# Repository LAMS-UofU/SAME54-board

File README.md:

# LAMS 

In these files, you will find the software, datasheets and PCB design for the LAMS project. We integrated multiple peripherals to use with our needed devices such as: timers for the servo PWM signal, UART communications for the LiDAR, simple GPIO signals for a status LED, as well as a simple SysTick configuration to give precise timing measurements. 

## Pinouts

LiDAR: Tx (PA04) / Rx (PA05) / PWM (PB09) <br>
Servo: PWM (PA07) <br>
SD Card: CMD (PA20) / CLK (PA21) / DAT0 (PB18) / DAT1 (PB19) / DAT2 (PB20) / DAT3 (PB21) / CD (PD20) / WP (PD21) <br>
Status LED: PA06 <br>
Start Button: PA27 <br>

## Resources

### SAME54

[SAM D5X/E5X Family Datasheet](http://ww1.microchip.com/downloads/en/DeviceDoc/SAM_D5xE5x_Family_Data_Sheet_DS60001507F.pdf) <br>
[SAM E54 Xplained Pro User's Guide](http://ww1.microchip.com/downloads/en/DeviceDoc/70005321A.pdf)

### Peripherals

[RPLiDAR A2M8 Datasheet](https://cdn.sparkfun.com/assets/e/a/f/9/8/LD208_SLAMTEC_rplidar_datasheet_A2M8_v1.0_en.pdf) <br>
[RPLiDAR A2M8 Communications Protocol v1.0](https://www.robotshop.com/media/files/pdf2/rpk-02-communication-protocol.pdf) <br>
[RPLiDAR A2M8 Communications Protocol v2.1](http://bucket.download.slamtec.com/ccb3c2fc1e66bb00bd4370e208b670217c8b55fa/LR001_SLAMTEC_rplidar_protocol_v2.1_en.pdf) <br>
[SPT5435-180 Specifications](http://www.spt-servo.com/Product/015234339.html)

### MISC

[ASF4 API Reference Manual](http://ww1.microchip.com/downloads/en/DeviceDoc/50002633B.pdf)

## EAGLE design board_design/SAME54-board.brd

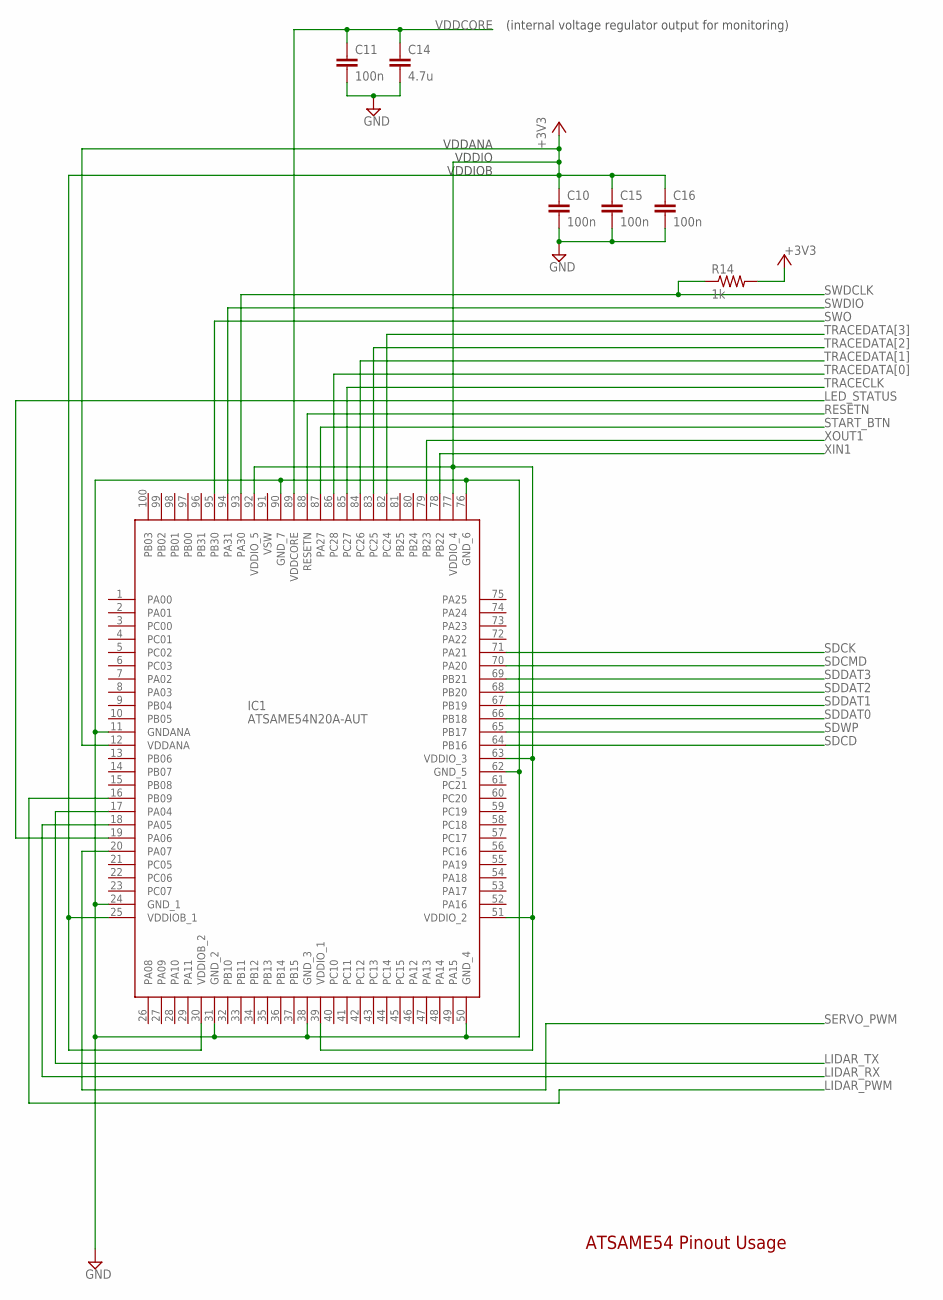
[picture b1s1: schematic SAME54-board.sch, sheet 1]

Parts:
C10, C11, C15, C16: 100n; C0603
C14: 4.7u; C0603
IC1: ATSAME54N20A-AUT; QFP50P1600X1600X120-100N
R14: 1k; R0603

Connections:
+3V3: C10.1, C15.1, C16.1, IC1.12 (VDDANA), IC1.25 (VDDIOB_1), IC1.30 (VDDIOB_2), IC1.39 (VDDIO_1), IC1.51 (VDDIO_2), IC1.63 (VDDIO_3), IC1.77 (VDDIO_4), IC1.92 (VDDIO_5), R14.2; also elsewhere on the board
GND: C10.2, C11.2, C14.2, C15.2, C16.2, IC1.11 (GNDANA), IC1.24 (GND_1), IC1.31 (GND_2), IC1.38 (GND_3), IC1.50 (GND_4), IC1.62 (GND_5), IC1.76 (GND_6), IC1.90 (GND_7); also elsewhere on the board
LED_STATUS: IC1.19 (PA06); also elsewhere on the board
LIDAR_PWM: IC1.16 (PB09); also elsewhere on the board
LIDAR_RX: IC1.18 (PA05); also elsewhere on the board
LIDAR_TX: IC1.17 (PA04); also elsewhere on the board
RESETN: IC1.88 (RESETN); also elsewhere on the board
SDCD: IC1.64 (PB16); also elsewhere on the board
SDCK: IC1.71 (PA21); also elsewhere on the board
SDCMD: IC1.70 (PA20); also elsewhere on the board
SDDAT0: IC1.66 (PB18); also elsewhere on the board
SDDAT1: IC1.67 (PB19); also elsewhere on the board
SDDAT2: IC1.68 (PB20); also elsewhere on the board
SDDAT3: IC1.69 (PB21); also elsewhere on the board
SDWP: IC1.65 (PB17); also elsewhere on the board
SERVO_PWM: IC1.20 (PA07); also elsewhere on the board
START_BTN: IC1.87 (PA27); also elsewhere on the board
SWDCLK: IC1.93 (PA30), R14.1; also elsewhere on the board
SWDIO: IC1.94 (PA31); also elsewhere on the board
SWO: IC1.95 (PB30); also elsewhere on the board
TRACECLK: IC1.85 (PC27); also elsewhere on the board
TRACEDATA[0]: IC1.86 (PC28); also elsewhere on the board
TRACEDATA[1]: IC1.84 (PC26); also elsewhere on the board
TRACEDATA[2]: IC1.83 (PC25); also elsewhere on the board
TRACEDATA[3]: IC1.82 (PC24); also elsewhere on the board
VDDCORE: C11.1, C14.1, IC1.89 (VDDCORE)
XIN1: IC1.78 (PB22); also elsewhere on the board
XOUT1: IC1.79 (PB23); also elsewhere on the board

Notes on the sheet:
ATSAME54 Pinout Usage
(internal voltage regulator output for monitoring)
VDDANA
VDDIO
VDDIOB

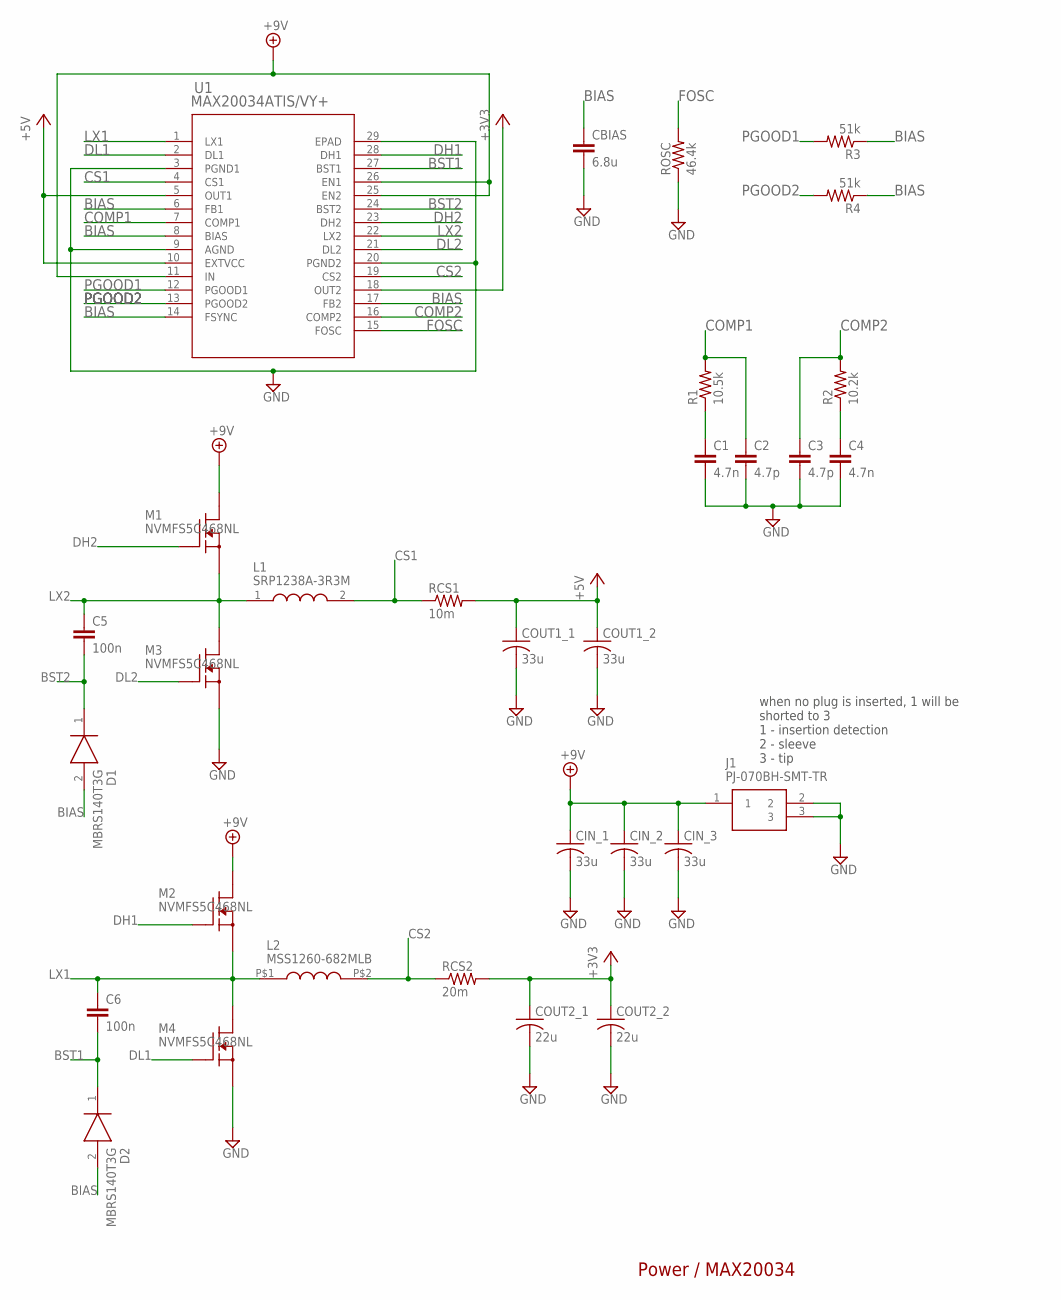
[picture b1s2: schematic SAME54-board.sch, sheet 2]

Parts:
C1, C4: 4.7n; C0603
C2, C3: 4.7p; C0402
C5, C6: 100n; C0603
CBIAS: 6.8u; C1206
CIN_1, CIN_2, CIN_3: 33u; C1812
COUT1_1, COUT1_2: 33u; C1812
COUT2_1, COUT2_2: 22u; C1206
D1, D2: MBRS140T3G; DIOM5436X247N
J1: PJ-070BH-SMT-TR; PJ070BHSMTTR
L1: SRP1238A-3R3M; INDPM135125X350N
L2: MSS1260-682MLB; MSS1260
M1, M2, M3, M4: NVMFS5C468NL; DFN5_SO-8FL
R1: 10.5k; R0402
R2: 10.2k; R0402
R3, R4: 51k; R0402
RCS1: 10m; R0603
RCS2: 20m; R1206
ROSC: 46.4k; R0402
U1: MAX20034ATIS/VY+; 21-100130_MXM

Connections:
+3V3: COUT2_1.1, COUT2_2.1, RCS2.2, U1.18 (OUT2); also elsewhere on the board
+5V: COUT1_1.1, COUT1_2.1, RCS1.2, U1.5 (OUT1), U1.10 (EXTVCC); also elsewhere on the board
+9V: CIN_1.1, CIN_2.1, CIN_3.1, J1.1, M1.D1 (D), M1.D2 (D), M1.D3 (D), M1.D4 (D), M2.D1 (D), M2.D2 (D), M2.D3 (D), M2.D4 (D), U1.11 (IN), U1.25 (EN2), U1.26 (EN1)
BIAS: CBIAS.1, D1.2 (A), D2.2 (A), R3.1, R4.1, U1.6 (FB1), U1.8 (BIAS), U1.14 (FSYNC), U1.17 (FB2)
BST1: C6.2, D2.1 (K), U1.27 (BST1)
BST2: C5.2, D1.1 (K), U1.24 (BST2)
COMP1: C2.1, R1.2, U1.7 (COMP1)
COMP2: C3.1, R2.2, U1.16 (COMP2)
CS1: L1.2, RCS1.1, U1.4 (CS1)
CS2: L2.P$2 (2), RCS2.1, U1.19 (CS2)
DH1: M2.G, U1.28 (DH1)
DH2: M1.G, U1.23 (DH2)
DL1: M4.G, U1.2 (DL1)
DL2: M3.G, U1.21 (DL2)
FOSC: ROSC.2, U1.15 (FOSC)
GND: C1.2, C2.2, C3.2, C4.2, CBIAS.2, CIN_1.2, CIN_2.2, CIN_3.2, COUT1_1.2, COUT1_2.2, COUT2_1.2, COUT2_2.2, J1.2, J1.3, M3.S1 (S), M3.S2 (S), M3.S3 (S), M4.S1 (S), M4.S2 (S), M4.S3 (S), ROSC.1, U1.3 (PGND1), U1.9 (AGND), U1.20 (PGND2), U1.29 (EPAD); also elsewhere on the board
LX1: C6.1, L2.P$1 (1), M2.S1 (S), M2.S2 (S), M2.S3 (S), M4.D1 (D), M4.D2 (D), M4.D3 (D), M4.D4 (D), U1.1 (LX1)
LX2: C5.1, L1.1, M1.S1 (S), M1.S2 (S), M1.S3 (S), M3.D1 (D), M3.D2 (D), M3.D3 (D), M3.D4 (D), U1.22 (LX2)
unnamed: C1.1, R1.1
unnamed: C4.1, R2.1
PGOOD1: R3.2, U1.12 (PGOOD1)
PGOOD2: R4.2, U1.13 (PGOOD2)

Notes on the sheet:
Power / MAX20034
when no plug is inserted, 1 will be shorted to 3 1 - insertion detection 2 - sleeve 3 - tip

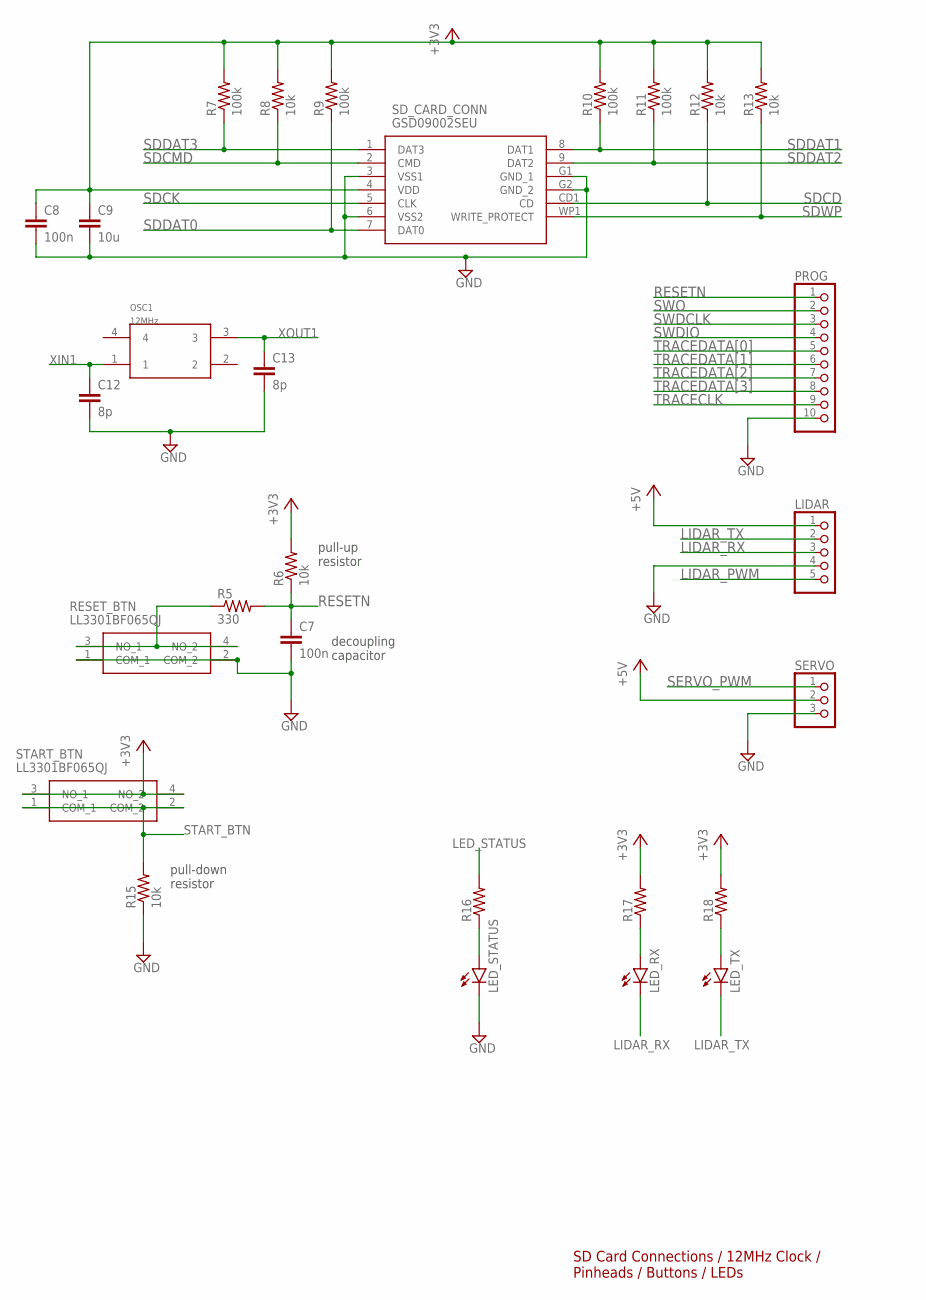
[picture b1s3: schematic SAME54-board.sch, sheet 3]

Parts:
C7, C8: 100n; C0603
C9: 10u; C0603
C12, C13: 8p; C0603
LED_RX: LEDCHIPLED_0603; CHIPLED_0603
LED_STATUS: LEDCHIPLED_0603; CHIPLED_0603
LED_TX: LEDCHIPLED_0603; CHIPLED_0603
LIDAR: PINHD-1X5; 1X05
OSC1: CX3225CA12000D0KPSC1CX3225CA; OSCCC320X250X90N
PROG: PINHD-1X10; 1X10
R5: 330; R0603
R6, R8, R12, R13, R15: 10k; R0603
R7, R9, R10, R11: 100k; R0603
R16, R17, R18: R-US_R0603; R0603
RESET_BTN: LL3301BF065QJ
SD_CARD_CONN: GSD09002SEU
SERVO: PINHD-1X3; 1X03
START_BTN: LL3301BF065QJ

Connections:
+3V3: C8.1, C9.1, R6.2, R7.2, R8.2, R9.2, R10.2, R11.2, R12.2, R13.2, R17.2, R18.2, SD_CARD_CONN.4 (VDD), START_BTN.3 (NO_1), START_BTN.4 (NO_2); also elsewhere on the board
+5V: LIDAR.1, SERVO.2; also elsewhere on the board
GND: C7.2, C8.2, C9.2, C12.2, C13.2, LED_STATUS.C, LIDAR.4, PROG.10, R15.1, RESET_BTN.1 (COM_1), RESET_BTN.2 (COM_2), SD_CARD_CONN.3 (VSS1), SD_CARD_CONN.6 (VSS2), SD_CARD_CONN.G1 (GND_1), SD_CARD_CONN.G2 (GND_2), SERVO.3; also elsewhere on the board
LED_STATUS: R16.2; also elsewhere on the board
LIDAR_PWM: LIDAR.5; also elsewhere on the board
LIDAR_RX: LED_RX.C, LIDAR.3; also elsewhere on the board
LIDAR_TX: LED_TX.C, LIDAR.2; also elsewhere on the board
unnamed: LED_STATUS.A, R16.1
unnamed: R5.1, RESET_BTN.3 (NO_1), RESET_BTN.4 (NO_2)
unnamed: LED_RX.A, R17.1
unnamed: LED_TX.A, R18.1
RESETN: C7.1, PROG.1, R5.2, R6.1; also elsewhere on the board
SDCD: R12.1, SD_CARD_CONN.CD1 (CD); also elsewhere on the board
SDCK: SD_CARD_CONN.5 (CLK); also elsewhere on the board
SDCMD: R8.1, SD_CARD_CONN.2 (CMD); also elsewhere on the board
SDDAT0: R9.1, SD_CARD_CONN.7 (DAT0); also elsewhere on the board
SDDAT1: R10.1, SD_CARD_CONN.8 (DAT1); also elsewhere on the board
SDDAT2: R11.1, SD_CARD_CONN.9 (DAT2); also elsewhere on the board
SDDAT3: R7.1, SD_CARD_CONN.1 (DAT3); also elsewhere on the board
SDWP: R13.1, SD_CARD_CONN.WP1 (WRITE_PROTECT); also elsewhere on the board
SERVO_PWM: SERVO.1; also elsewhere on the board
START_BTN: R15.2, START_BTN.1 (COM_1), START_BTN.2 (COM_2); also elsewhere on the board
SWDCLK: PROG.3; also elsewhere on the board
SWDIO: PROG.4; also elsewhere on the board
SWO: PROG.2; also elsewhere on the board
TRACECLK: PROG.9; also elsewhere on the board
TRACEDATA[0]: PROG.5; also elsewhere on the board
TRACEDATA[1]: PROG.6; also elsewhere on the board
TRACEDATA[2]: PROG.7; also elsewhere on the board
TRACEDATA[3]: PROG.8; also elsewhere on the board
XIN1: C12.1, OSC1.1; also elsewhere on the board
XOUT1: C13.1, OSC1.3; also elsewhere on the board

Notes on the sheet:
SD Card Connections / 12MHz Clock / Pinheads / Buttons / LEDs
decoupling capacitor
pull-up resistor
pull-down resistor

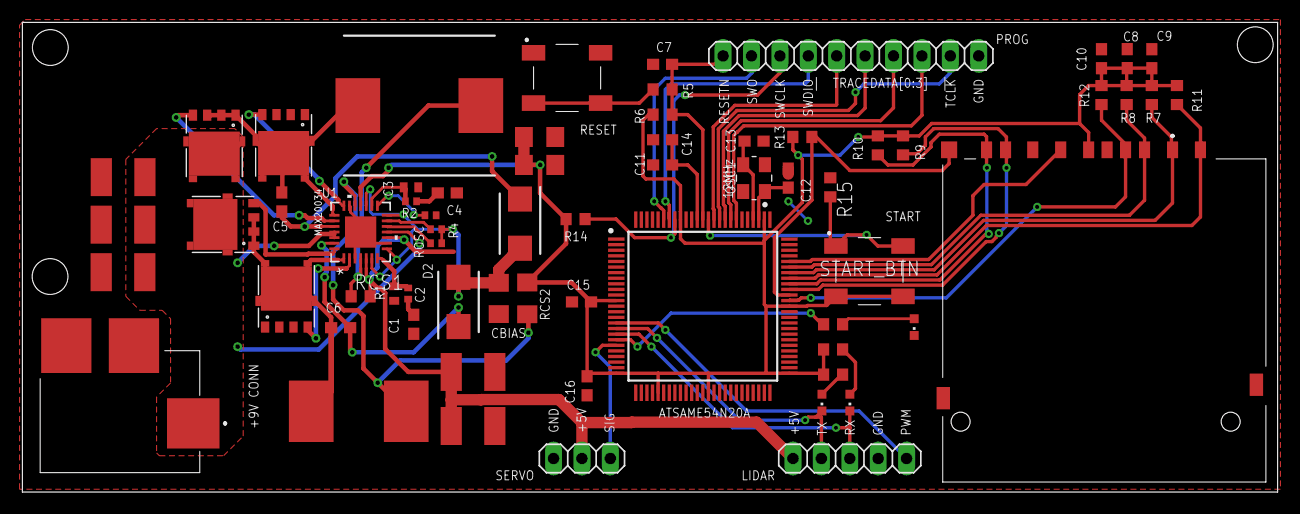
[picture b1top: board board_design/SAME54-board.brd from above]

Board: 2 copper layers, 112.2 x 42.0 mm, 66 parts (0 on the bottom side), 52 nets.

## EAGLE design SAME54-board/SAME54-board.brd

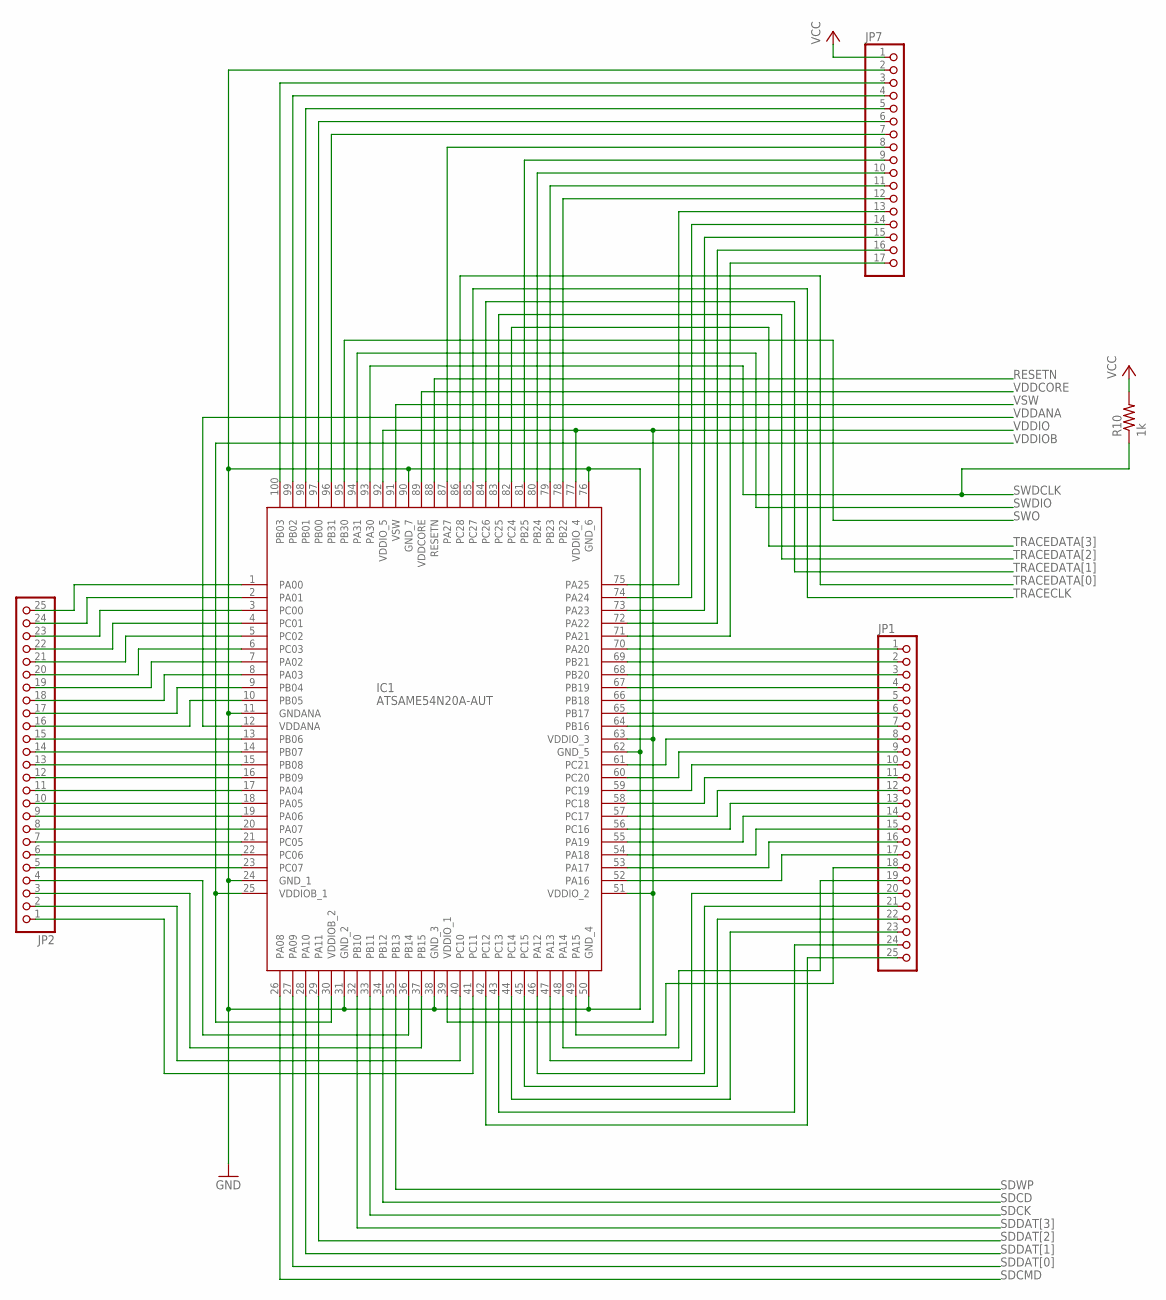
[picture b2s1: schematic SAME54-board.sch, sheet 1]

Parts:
IC1: ATSAME54N20A-AUT; QFP50P1600X1600X120-100N
JP1, JP2: PINHD-1X25; 1X25
JP7: PINHD-1X17; 1X17
R10: 1k; M1206

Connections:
GND: IC1.11 (GNDANA), IC1.24 (GND_1), IC1.31 (GND_2), IC1.38 (GND_3), IC1.50 (GND_4), IC1.62 (GND_5), IC1.76 (GND_6), IC1.90 (GND_7), JP7.2; also elsewhere on the board
unnamed: IC1.23 (PC07), JP2.5
unnamed: IC1.22 (PC06), JP2.6
unnamed: IC1.21 (PC05), JP2.7
unnamed: IC1.20 (PA07), JP2.8
unnamed: IC1.19 (PA06), JP2.9
unnamed: IC1.18 (PA05), JP2.10
unnamed: IC1.17 (PA04), JP2.11
unnamed: IC1.16 (PB09), JP2.12
unnamed: IC1.15 (PB08), JP2.13
unnamed: IC1.14 (PB07), JP2.14
unnamed: IC1.13 (PB06), JP2.15
unnamed: IC1.10 (PB05), JP2.16
unnamed: IC1.9 (PB04), JP2.17
unnamed: IC1.8 (PA03), JP2.18
unnamed: IC1.7 (PA02), JP2.19
unnamed: IC1.6 (PC03), JP2.20
unnamed: IC1.5 (PC02), JP2.21
unnamed: IC1.4 (PC01), JP2.22
unnamed: IC1.3 (PC00), JP2.23
unnamed: IC1.2 (PA01), JP2.24
unnamed: IC1.73 (PA23), JP7.15
unnamed: IC1.70 (PA20), JP1.1
unnamed: IC1.69 (PB21), JP1.2
unnamed: IC1.68 (PB20), JP1.3
unnamed: IC1.67 (PB19), JP1.4
unnamed: IC1.66 (PB18), JP1.5
unnamed: IC1.65 (PB17), JP1.6
unnamed: IC1.64 (PB16), JP1.7
unnamed: IC1.61 (PC21), JP1.8
unnamed: IC1.60 (PC20), JP1.9
unnamed: IC1.59 (PC19), JP1.10
unnamed: IC1.58 (PC18), JP1.11
unnamed: IC1.57 (PC17), JP1.12
unnamed: IC1.56 (PC16), JP1.13
unnamed: IC1.55 (PA19), JP1.14
unnamed: IC1.54 (PA18), JP1.15
unnamed: IC1.53 (PA17), JP1.16
unnamed: IC1.52 (PA16), JP1.17
unnamed: IC1.49 (PA15), JP1.18
unnamed: IC1.48 (PA14), JP1.19
unnamed: IC1.41 (PC11), JP2.1
unnamed: IC1.47 (PA13), JP1.20
unnamed: IC1.46 (PA12), JP1.21
unnamed: IC1.45 (PC15), JP1.22
unnamed: IC1.44 (PC14), JP1.23
unnamed: IC1.43 (PC13), JP1.24
unnamed: IC1.42 (PC12), JP1.25
unnamed: IC1.40 (PC10), JP2.2
unnamed: IC1.37 (PB15), JP2.3
unnamed: IC1.36 (PB14), JP2.4
unnamed: IC1.1 (PA00), JP2.25
PA21: IC1.71 (PA21), JP7.17
PA22: IC1.72 (PA22), JP7.16
PA24: IC1.74 (PA24), JP7.14
PA25: IC1.75 (PA25), JP7.13
PA27: IC1.87 (PA27), JP7.8
PB0: IC1.97 (PB00), JP7.6
PB1: IC1.98 (PB01), JP7.5
PB2: IC1.99 (PB02), JP7.4
PB3: IC1.100 (PB03), JP7.3
PB22: IC1.78 (PB22), JP7.12
PB23: IC1.79 (PB23), JP7.11
PB24: IC1.80 (PB24), JP7.10
PB25: IC1.81 (PB25), JP7.9
PB31: IC1.96 (PB31), JP7.7
RESETN: IC1.88 (RESETN); also elsewhere on the board
SDCD: IC1.34 (PB12); also elsewhere on the board
SDCK: IC1.33 (PB11); also elsewhere on the board
SDCMD: IC1.26 (PA08)
SDDAT[0]: IC1.27 (PA09); also elsewhere on the board
SDDAT[1]: IC1.28 (PA10); also elsewhere on the board
SDDAT[2]: IC1.29 (PA11); also elsewhere on the board
SDDAT[3]: IC1.32 (PB10); also elsewhere on the board
SDWP: IC1.35 (PB13); also elsewhere on the board
SWDCLK: IC1.93 (PA30), R10.1; also elsewhere on the board
SWDIO: IC1.94 (PA31); also elsewhere on the board
SWO: IC1.95 (PB30); also elsewhere on the board
TRACECLK: IC1.85 (PC27); also elsewhere on the board
TRACEDATA[0]: IC1.86 (PC28); also elsewhere on the board
TRACEDATA[1]: IC1.84 (PC26); also elsewhere on the board
TRACEDATA[2]: IC1.83 (PC25); also elsewhere on the board
TRACEDATA[3]: IC1.82 (PC24); also elsewhere on the board
VCC: JP7.1, R10.2; also elsewhere on the board
VDDANA: IC1.12 (VDDANA); also elsewhere on the board
VDDCORE: IC1.89 (VDDCORE); also elsewhere on the board
VDDIO: IC1.39 (VDDIO_1), IC1.51 (VDDIO_2), IC1.63 (VDDIO_3), IC1.77 (VDDIO_4), IC1.92 (VDDIO_5); also elsewhere on the board
VDDIOB: IC1.25 (VDDIOB_1), IC1.30 (VDDIOB_2); also elsewhere on the board
VSW: IC1.91 (VSW); also elsewhere on the board

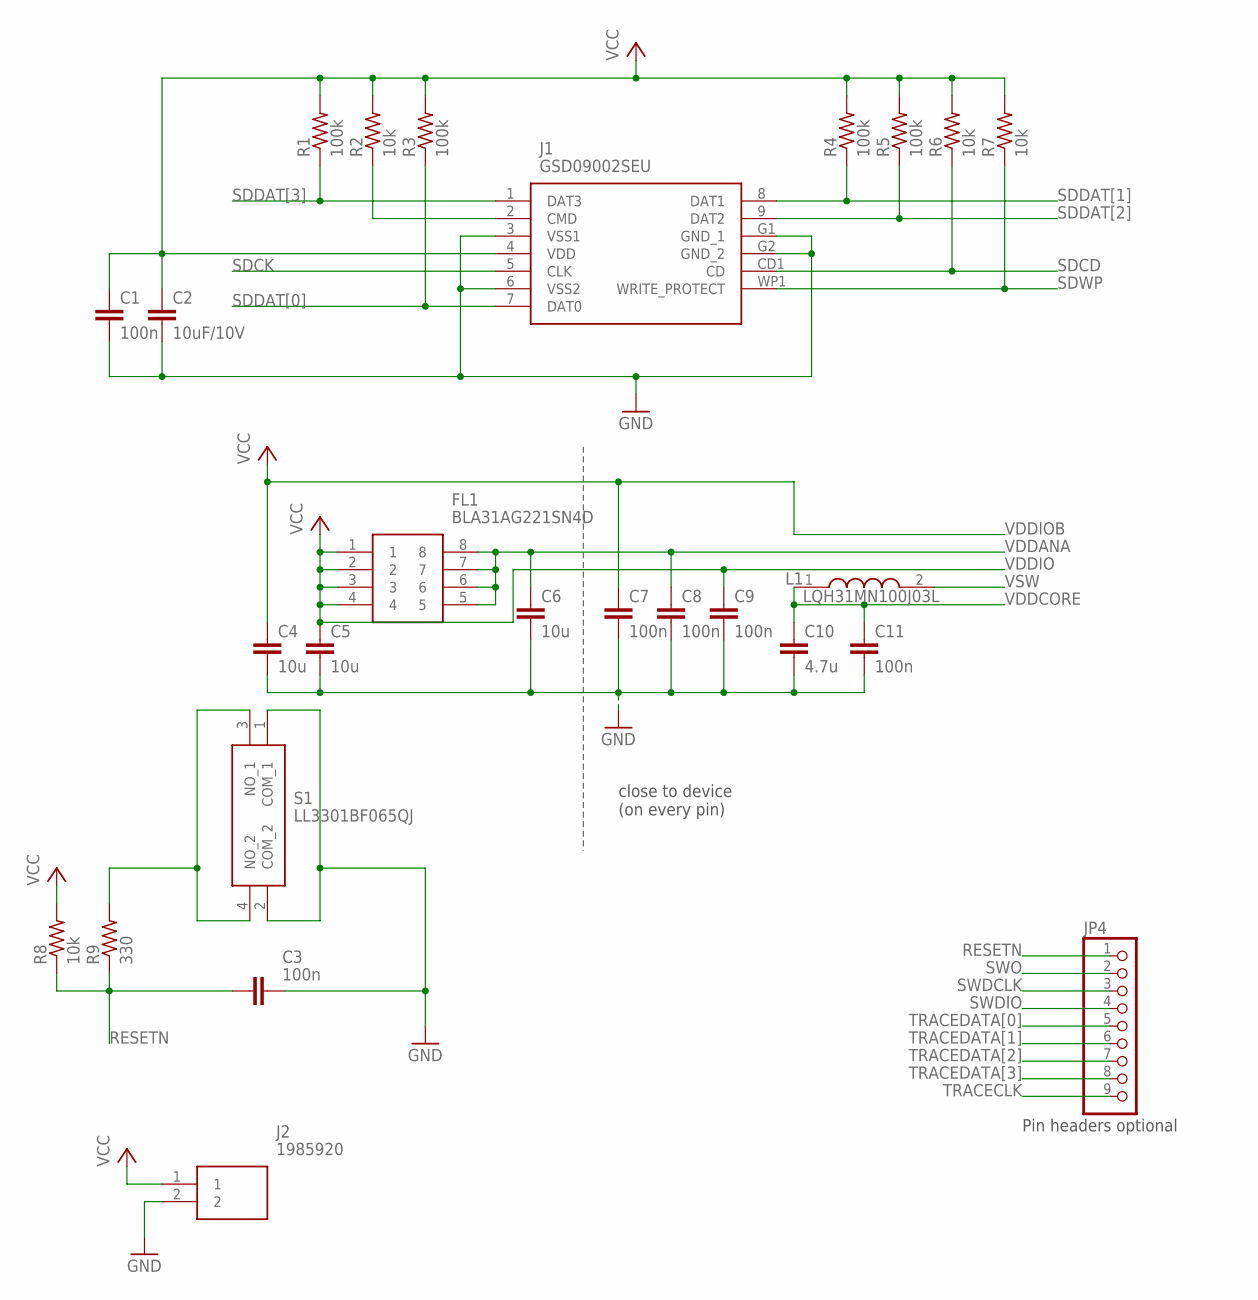
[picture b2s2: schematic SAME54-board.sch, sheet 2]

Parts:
C1, C3, C7, C8, C9, C11: 100n; C1206
C2: 10uF/10V; C1206
C4, C5, C6: 10u; C1206
C10: 4.7u; C1206
FL1: BLA31AG221SN4D; BLA31AG102SN4D
J1: GSD09002SEU
J2: 1985920; SHDR2W110P0X500_1X2_1000X950X1
JP4: PINHD-1X9; 1X09
L1: LQH31MN100J03L; LQH31CN100K03L
R1, R3, R4, R5: 100k; M1206
R2, R6, R7, R8: 10k; M1206
R9: 330; M1206
S1: LL3301BF065QJ

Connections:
GND: C1.2, C2.2, C3.2, C4.2, C5.2, C6.2, C7.2, C8.2, C9.2, C10.2, C11.2, J1.3 (VSS1), J1.6 (VSS2), J1.G1 (GND_1), J1.G2 (GND_2), J2.2, S1.1 (COM_1), S1.2 (COM_2); also elsewhere on the board
unnamed: J1.2 (CMD), R2.1
unnamed: R9.2, S1.3 (NO_1), S1.4 (NO_2)
RESETN: C3.1, JP4.1, R8.1, R9.1; also elsewhere on the board
SDCD: J1.CD1 (CD), R6.1; also elsewhere on the board
SDCK: J1.5 (CLK); also elsewhere on the board
SDDAT[0]: J1.7 (DAT0), R3.1; also elsewhere on the board
SDDAT[1]: J1.8 (DAT1), R4.1; also elsewhere on the board
SDDAT[2]: J1.9 (DAT2), R5.1; also elsewhere on the board
SDDAT[3]: J1.1 (DAT3), R1.1; also elsewhere on the board
SDWP: J1.WP1 (WRITE_PROTECT), R7.1; also elsewhere on the board
SWDCLK: JP4.3; also elsewhere on the board
SWDIO: JP4.4; also elsewhere on the board
SWO: JP4.2; also elsewhere on the board
TRACECLK: JP4.9; also elsewhere on the board
TRACEDATA[0]: JP4.5; also elsewhere on the board
TRACEDATA[1]: JP4.6; also elsewhere on the board
TRACEDATA[2]: JP4.7; also elsewhere on the board
TRACEDATA[3]: JP4.8; also elsewhere on the board
VCC: C1.1, C2.1, J1.4 (VDD), J2.1, R1.2, R2.2, R3.2, R4.2, R5.2, R6.2, R7.2, R8.2; also elsewhere on the board
VDDANA: C6.1, C8.1, FL1.5, FL1.6, FL1.7, FL1.8; also elsewhere on the board
VDDCORE: C10.1, C11.1, L1.1; also elsewhere on the board
VDDIO: C5.1, C9.1, FL1.1, FL1.2, FL1.3, FL1.4; also elsewhere on the board
VDDIOB: C4.1, C7.1; also elsewhere on the board
VSW: L1.2; also elsewhere on the board

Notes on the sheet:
close to device (on every pin)
Pin headers optional

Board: 2 copper layers, 31 parts (0 on the bottom side), 90 nets, no tracks yet.

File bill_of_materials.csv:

Part,Quantity,Mouser Part #,Manufacturer Part #,Manufacturer,Description,Datasheet
IC1,1,556-ATSAME54N20AAUT,ATSAME54N20A-AUT,Microchip,ARM Microcontrollers - MCU 120MHZ 1024KB FLASH 100 TQFP PKG IN 85C,https://www.mouser.com/ds/2/268/60001507A-1130176.pdf
"R1,R3,R4,R5",4,71-CRCW1206J-100K-E3,CRCW1206100KJNEA,Vishay/Dale,Thick Film Resistors - SMD 1/4watt 100Kohms 5%,https://www.mouser.com/datasheet/2/427/dcrcwe3-1762152.pdf
"R2,R6,R7,R8",4,71-CRCW1206J-10K-E3,CRCW120610K0JNEA,Vishay/Dale,Thick Film Resistors - SMD 1/4watt 10Kohms 5%,https://www.mouser.com/datasheet/2/427/dcrcwe3-1762152.pdf
R9,1,71-CRCW1206J-330-E3,CRCW1206330RJNEA,Vishay/Dale,Thick Film Resistors - SMD 1/4watt 330ohms 5%,https://www.mouser.com/datasheet/2/427/dcrcwe3-1762152.pdf
R10,1,71-CRCW1206J-1K-E3,CRCW12061K00JNEA,Vishay/Dale,Thick Film Resistors - SMD 1/4watt 1Kohms 5%,https://www.mouser.com/datasheet/2/427/dcrcwe3-1762152.pdf
"C1,C3,C7,C8,C9,C11",6,603-AS1206KKX7YBB104,AS1206KKX7RYBB104,Yageo,Multilayer Ceramic Capacitors MLCC - SMD/SMT 0.1uF 10% 250V AEC-Q200,https://www.mouser.com/datasheet/2/447/yageodocoutput-1313910.pdf
"C2,C4,C5",3,603-CC206KKX5R7BB106,CC1206KKX5R7BB106,Yageo,Multilayer Ceramic Capacitors MLCC - SMD/SMT 10uF 10% 16V,https://www.mouser.com/datasheet/2/447/UPY-GPHC_X5R_4V-to-50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
C10,1,603-CC206KKX5R9BB475,CC1206KKX5R9BB475,Yageo,Multilayer Ceramic Capacitors MLCC - SMD/SMT 4.7M pF 10% 50 Volts,https://www.mouser.com/datasheet/2/447/UPY-GPHC_X5R_4V-to-50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
FL1,1,81-BLA31AG221SN4D,BLA31AG221SN4D,Murata Electronics,"Murata Power Solutions Ferrite Bead, 3.2 x 1.6 x 0.8mm (3216), 220 impedance at 100 MHz",https://componentsearchengine.com/Datasheets/1/BLA31AG221SN4D.pdf
J1,1,523-GSD09002SEU,GSD09002SEU,Amphenol,"Memory Card Connectors SD, 9 pos, 15U",https://www.arrow.com/en/products/gsd09002seu/amphenol
J2,1,651-1985920 ,1985920,Phoenix Contact,"Screw terminal, 5mm pitch",https://www.mouser.com/datasheet/2/324/985920-1459071.pdf
L1,1,81-LQH31MN100J03L,LQH31MN100J03L,Murata Electronics,Fixed Inductors 1206 10uH +/-5% Chip Inductor,https://www.mouser.com/datasheet/2/281/JELF243A-0162-1699505.pdf
S1,1,612-LL3301BF065QJ,LL3301BF065QJ,E-Switch,Pushbutton Switches 50mA 12VDC F065 9.5mm J-Lead,http://spec_sheets.e-switch.com/specs/P010455.pdf
"JP1,JP2,JP4,JP7",3,649-68001-121HLF ,68001-121HLF ,Amphenol FCI,"20-pin header, 2.54mm spacing",https://www.mouser.com/datasheet/2/18/68000-1266375.pdf

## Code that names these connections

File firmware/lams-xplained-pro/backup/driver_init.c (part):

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void LIDAR_USART_PORT_init(void)
{

	gpio_set_pin_function(PA04, PINMUX_PA04D_SERCOM0_PAD0);

	gpio_set_pin_function(PA05, PINMUX_PA05D_SERCOM0_PAD1);
}

void LIDAR_USART_CLOCK_init(void)
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void STDIO_IO_PORT_init(void)
{

	gpio_set_pin_function(PB25, PINMUX_PB25D_SERCOM2_PAD0);

	gpio_set_pin_function(PB24, PINMUX_PB24D_SERCOM2_PAD1);
}

void STDIO_IO_CLOCK_init(void)
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void SDHC_IO_BUS_PORT_init(void)
{

	gpio_set_pin_direction(PA21,
	                       // <y> Pin direction
	                       // <id> pad_direction
	                       // <GPIO_DIRECTION_OFF"> Off
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	                       // <GPIO_DIRECTION_OUT"> Out
	                       GPIO_DIRECTION_OUT);

	gpio_set_pin_level(PA21,
	                   // <y> Initial level
	                   // <id> pad_initial_level
	                   // <false"> Low
	                   // <true"> High
	                   false);

	gpio_set_pin_pull_mode(PA21,
	                       // <y> Pull configuration
	                       // <id> pad_pull_config
	                       // <GPIO_PULL_OFF"> Off
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	                       // <GPIO_PULL_DOWN"> Pull-down
	                       GPIO_PULL_OFF);

	gpio_set_pin_function(PA21,
	                      // <y> Pin function
	                      // <id> pad_function
	                      // <i> Auto : use driver pinmux if signal is imported by driver, else turn off function
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	                      // <GPIO_PIN_FUNCTION_N"> N
	                      PINMUX_PA21I_SDHC1_SDCK);

	gpio_set_pin_direction(PA20,
	                       // <y> Pin direction
	                       // <id> pad_direction
	                       // <GPIO_DIRECTION_OFF"> Off
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	                       // <GPIO_DIRECTION_OUT"> Out
	                       GPIO_DIRECTION_OUT);

	gpio_set_pin_level(PA20,
	                   // <y> Initial level
	                   // <id> pad_initial_level
	                   // <false"> Low
	                   // <true"> High
	                   false);

	gpio_set_pin_pull_mode(PA20,
	                       // <y> Pull configuration
	                       // <id> pad_pull_config
	                       // <GPIO_PULL_OFF"> Off
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	                       // <GPIO_PULL_DOWN"> Pull-down
	                       GPIO_PULL_OFF);

	gpio_set_pin_function(PA20,
	                      // <y> Pin function
	                      // <id> pad_function
	                      // <i> Auto : use driver pinmux if signal is imported by driver, else turn off function
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	                      // <GPIO_PIN_FUNCTION_N"> N
	                      PINMUX_PA20I_SDHC1_SDCMD);

	gpio_set_pin_direction(PB18,
	                       // <y> Pin direction
	                       // <id> pad_direction
	                       // <GPIO_DIRECTION_OFF"> Off
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	                       // <GPIO_DIRECTION_OUT"> Out
	                       GPIO_DIRECTION_OUT);

	gpio_set_pin_level(PB18,
	                   // <y> Initial level
	                   // <id> pad_initial_level
	                   // <false"> Low
	                   // <true"> High
	                   false);

	gpio_set_pin_pull_mode(PB18,
	                       // <y> Pull configuration
	                       // <id> pad_pull_config
	                       // <GPIO_PULL_OFF"> Off
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	                       // <GPIO_PULL_DOWN"> Pull-down
	                       GPIO_PULL_OFF);

	gpio_set_pin_function(PB18,
	                      // <y> Pin function
	                      // <id> pad_function
	                      // <i> Auto : use driver pinmux if signal is imported by driver, else turn off function
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	                      // <GPIO_PIN_FUNCTION_N"> N
	                      PINMUX_PB18I_SDHC1_SDDAT0);

	gpio_set_pin_direction(PB19,
	                       // <y> Pin direction
	                       // <id> pad_direction
	                       // <GPIO_DIRECTION_OFF"> Off
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	                       // <GPIO_DIRECTION_OUT"> Out
	                       GPIO_DIRECTION_OUT);

	gpio_set_pin_level(PB19,
	                   // <y> Initial level
	                   // <id> pad_initial_level
	                   // <false"> Low
	                   // <true"> High
	                   false);

	gpio_set_pin_pull_mode(PB19,
	                       // <y> Pull configuration
	                       // <id> pad_pull_config
	                       // <GPIO_PULL_OFF"> Off
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	                       // <GPIO_PULL_DOWN"> Pull-down
	                       GPIO_PULL_OFF);

	gpio_set_pin_function(PB19,
	                      // <y> Pin function
	                      // <id> pad_function
	                      // <i> Auto : use driver pinmux if signal is imported by driver, else turn off function
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	                      // <GPIO_PIN_FUNCTION_N"> N
	                      PINMUX_PB19I_SDHC1_SDDAT1);

	gpio_set_pin_direction(PB20,
	                       // <y> Pin direction
	                       // <id> pad_direction
	                       // <GPIO_DIRECTION_OFF"> Off
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	                       // <GPIO_DIRECTION_OUT"> Out
	                       GPIO_DIRECTION_OUT);

	gpio_set_pin_level(PB20,
	                   // <y> Initial level
	                   // <id> pad_initial_level
	                   // <false"> Low
	                   // <true"> High
	                   false);

	gpio_set_pin_pull_mode(PB20,
	                       // <y> Pull configuration
	                       // <id> pad_pull_config
	                       // <GPIO_PULL_OFF"> Off
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	                       // <GPIO_PULL_DOWN"> Pull-down
	                       GPIO_PULL_OFF);

	gpio_set_pin_function(PB20,
	                      // <y> Pin function
	                      // <id> pad_function
	                      // <i> Auto : use driver pinmux if signal is imported by driver, else turn off function
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	                      // <GPIO_PIN_FUNCTION_N"> N
	                      PINMUX_PB20I_SDHC1_SDDAT2);

	gpio_set_pin_direction(PB21,
	                       // <y> Pin direction
	                       // <id> pad_direction
	                       // <GPIO_DIRECTION_OFF"> Off
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	                       // <GPIO_DIRECTION_OUT"> Out
	                       GPIO_DIRECTION_OUT);

	gpio_set_pin_level(PB21,
	                   // <y> Initial level
	                   // <id> pad_initial_level
	                   // <false"> Low
	                   // <true"> High
	                   false);

	gpio_set_pin_pull_mode(PB21,
	                       // <y> Pull configuration
	                       // <id> pad_pull_config
	                       // <GPIO_PULL_OFF"> Off
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	                       // <GPIO_PULL_DOWN"> Pull-down
	                       GPIO_PULL_OFF);

	gpio_set_pin_function(PB21,
	                      // <y> Pin function
	                      // <id> pad_function
	                      // <i> Auto : use driver pinmux if signal is imported by driver, else turn off function
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void SERVO_PWM_PORT_init(void)
{

	gpio_set_pin_function(PA07, PINMUX_PA07E_TC1_WO1);
}

void SERVO_PWM_CLOCK_init(void)
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void LIDAR_PWM_PORT_init(void)
{

	gpio_set_pin_function(PB08, PINMUX_PB08E_TC4_WO0);

	gpio_set_pin_function(PB09, PINMUX_PB09E_TC4_WO1);
}

void LIDAR_PWM_CLOCK_init(void)
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{
	init_mcu();

	// GPIO on PA06

	gpio_set_pin_level(LED_STATUS,
	                   // <y> Initial level
	                   // <id> pad_initial_level
	                   // <false"> Low
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	                   false);

	// Set pin direction to output
	gpio_set_pin_direction(LED_STATUS, GPIO_DIRECTION_OUT);

	gpio_set_pin_function(LED_STATUS, GPIO_PIN_FUNCTION_OFF);

	// GPIO on PA27

	// Set pin direction to input
	gpio_set_pin_direction(START_BTN, GPIO_DIRECTION_IN);

	gpio_set_pin_pull_mode(START_BTN,
	                       // <y> Pull configuration
	                       // <id> pad_pull_config
	                       // <GPIO_PULL_OFF"> Off
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	                       // <GPIO_PULL_DOWN"> Pull-down
	                       GPIO_PULL_OFF);

	gpio_set_pin_function(START_BTN, GPIO_PIN_FUNCTION_OFF);

	// GPIO on PC18

	gpio_set_pin_level(LED0,
	                   // <y> Initial level
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
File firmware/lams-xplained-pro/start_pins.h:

#ifndef START_PINS_H_
#define START_PINS_H_

#include <hal_gpio.h>

/* SAME54 has 14 pin functions */
#define GPIO_PIN_FUNCTION_A 0
#define GPIO_PIN_FUNCTION_B 1
#define GPIO_PIN_FUNCTION_C 2
#define GPIO_PIN_FUNCTION_D 3
#define GPIO_PIN_FUNCTION_E 4
#define GPIO_PIN_FUNCTION_F 5
#define GPIO_PIN_FUNCTION_G 6
#define GPIO_PIN_FUNCTION_H 7
#define GPIO_PIN_FUNCTION_I 8
#define GPIO_PIN_FUNCTION_J 9
#define GPIO_PIN_FUNCTION_K 10
#define GPIO_PIN_FUNCTION_L 11
#define GPIO_PIN_FUNCTION_M 12
#define GPIO_PIN_FUNCTION_N 13

/* STDIO_REDIRECT */
#define PB24 GPIO(GPIO_PORTB, 24)
#define PB25 GPIO(GPIO_PORTB, 25)

/* LIDAR */
#define PA04 GPIO(GPIO_PORTA, 4) /* USART : Tx */
#define PA05 GPIO(GPIO_PORTA, 5) /* USART : Rx */
#define PB09 GPIO(GPIO_PORTB, 9) /* PWM : WO/1 */

/* SERVO */
#define PA07 GPIO(GPIO_PORTA, 7) /* PWM : WO/1 */

/* SDMMC */
#define PA20 GPIO(GPIO_PORTA, 20) /* SDCMD   */
#define PA21 GPIO(GPIO_PORTA, 21) /* SDCK    */
#define PB18 GPIO(GPIO_PORTB, 18) /* SDDAT/0 */
#define PB19 GPIO(GPIO_PORTB, 19) /* SDDAT/1 */
#define PB20 GPIO(GPIO_PORTB, 20) /* SDDAT/2 */
#define PB21 GPIO(GPIO_PORTB, 21) /* SDDAT/3 */
#define CARD_DETECT_0 GPIO(GPIO_PORTD, 20)
#define WRITE_PROTECT_0 GPIO(GPIO_PORTD, 21)

/* GPIO */
#define START_BTN GPIO(GPIO_PORTA, 27)
#define LED_STATUS GPIO(GPIO_PORTA, 6)
#define LED0 GPIO(GPIO_PORTC, 18)

#endif // START_PINS_H_

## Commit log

2020-05-19 Added power supply, reset button and SDHC interface
2020-05-31 Designed board for all pre-determined peripherals needed.
2020-05-31 Added drill holes and correct power supply mistake
2020-05-31 Rotated R10 resistor text
2020-05-31 Added LAMS logo
2020-05-31 Removed molex adapters and recplaed with single pin hole for each signal
2020-05-31 New board design for better space managemnt
2020-06-01 Added bill of materials
2020-06-01 Added label for Reset and increased hole dimensions to 3.2mm
2020-06-01 Added Bill of Materials to README
2020-09-03 Starting new version of board. Bought Microchip development board--will only be printing final product
2020-09-28 Adding development board code and updated eagle files
2020-09-28 Updated gitignore
2020-10-02 Working PWM TC channels for both servo and lidar
2020-10-02 Updated README with pin configs for lidar's USART
2020-10-02 Added voltage regulator to block diagram
2020-10-22 Added power and max20034 to schematic
2020-10-22 Updated schematic to include i/o, sd card, 12MHz clock
2020-10-26 Finished custom SAME54 design. Ready to order
2020-11-05 Functioning LIDAR scanning and servo movement. Moving onto SD read/write
2020-11-05 Updated README
    Found out there is a v2.1 of communications protocol....
2020-11-07 Added comments and moved lidar/servo files into separate folders for organization
2020-11-07 Adjusted delays to use SysTick
2020-11-17 Added diskio and fatfs middleware for file writing
2020-11-18 Fully functional scan feature and writing to files
2020-11-28 Reformatted to take averages of samples per scan point
2020-11-28 Adjusted status light since there is no systick handler
2020-12-03 Adjusted servo to use double as angle measurements
2020-12-12 Add block-diagram
